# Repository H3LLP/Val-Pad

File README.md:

# Val Pad

A custom half-ish keyboard for gaming

I wanted to make something fun and that I could actually use daily, so I made this. I needed the desk space as well since my mouse didn't have much room to move around, so this is my solution.
  - Magnetically closing case
  - 19 switches
  - knob
  - gasket-mounted
  - https://www.printables.com/model/1851866-val-pad
  - Uses QMK Firmware(partly made with AI)

# Electric Bits

PCB Schematics

# BOM
|Designator                                                                               |Footprint                                                           |Quantity|Value                                             |Price |
|-----------------------------------------------------------------------------------------|--------------------------------------------------------------------|--------|--------------------------------------------------|------|
|D1, D10, D11, D12, D13, D14, D15, D16, D17, D18, D19, D2, D20, D3, D4, D5, D6, D7, D8, D9|D_DO-35_SOD27_P7.62mm_Horizontal                                    |20      |1N4148 (THT) Diode                                |$5    |
|S1, S10, S11, S12, S13, S14, S15, S16, S17, S18, S19, S2, S3, S4, S5, S6, S7, S8, S9     |MX_PCB_1.00u                                                        |19      |MX Switches                                       |$20   |
|SW1                                                                                      |RotaryEncoder_Alps_EC11E-Switch_Vertical_H20mm_CircularMountingHoles|1       |EC11 Rotary Encoder                               |$5    |
|U1                                                                                       |SOIC-28W_7.5x17.9mm_P1.27mm                                         |1       |MCP23017 Surface Mounted                          |$2    |
|U2                                                                                       |Seeed_XIAO_RP2040                                                   |1       |Seeed Xiao RP2040                                 |$7    |
|R1, R2                                                                                   |0603                                                                |2       |4.7 kΩ 0603 package 1/10 W surface-mount resistors|$3    |
|~                                                                                        |~                                                                   |1       |PCB                                               |$5    |
|~                                                                                        |~                                                                   |4       |4mm*2mm Circular Neodymium Magnets                |$10   |
|~                                                                                        |~                                                                   |4       |4mm*30mm Keyboard Gasket Strips                   |$7    |
|~                                                                                        |~                                                                   |4       |3D Printed Parts                                  |$10   |
|~                                                                                        |~                                                                   |4       |Macbook Pro Rubber Feet                           |$5    |
|~                                                                                        |~                                                                   |1       |Set of 2U PCB Mounted MX Stabilizers              |$10   |
|~                                                                                        |~                                                                   |15      |1U Keycaps                                        |varies|
|~                                                                                        |~                                                                   |1       |1.25U Keycaps                                     |varies|
|~                                                                                        |~                                                                   |2       |1.5U Keycaps                                      |varies|
|~                                                                                        |~                                                                   |1       |2U Keycap                                         |varies|
|~                                                                                        |~                                                                   |~       |~                                                 |Total $ 110-120|

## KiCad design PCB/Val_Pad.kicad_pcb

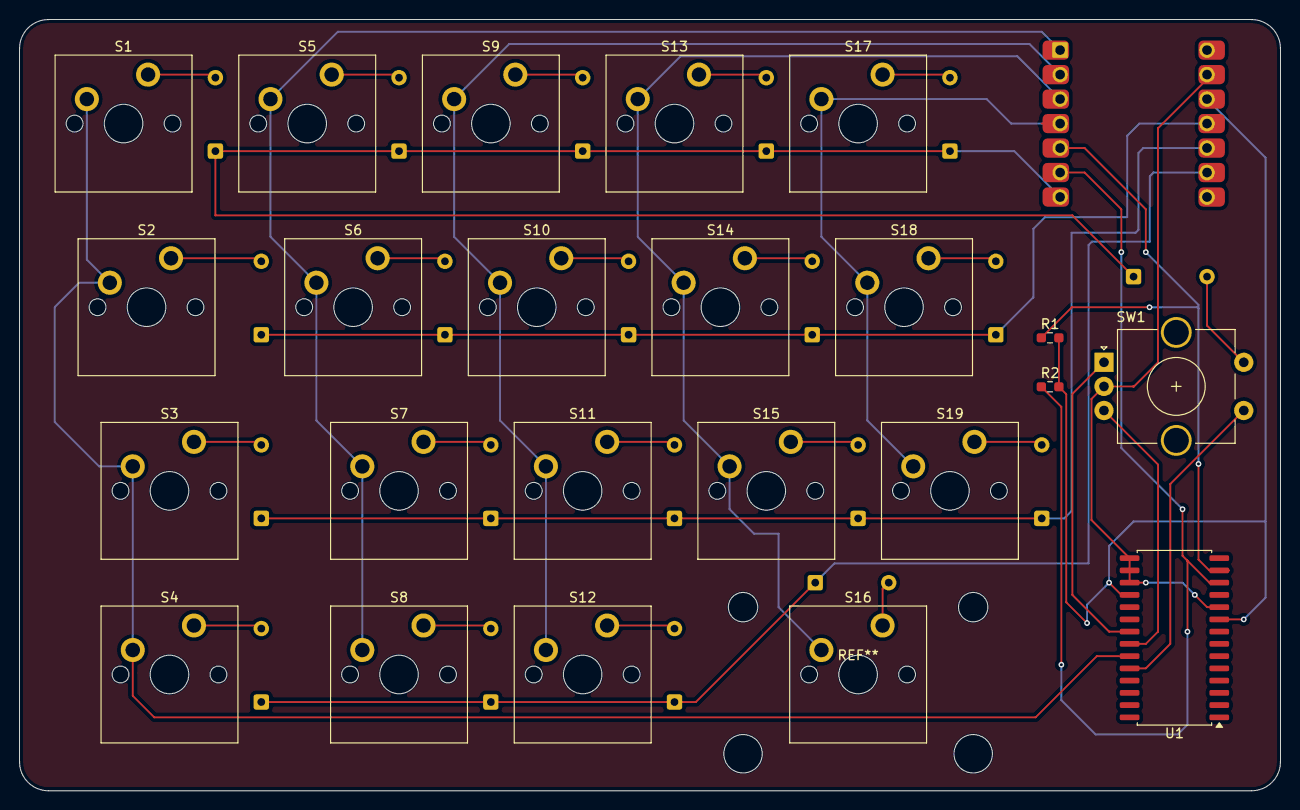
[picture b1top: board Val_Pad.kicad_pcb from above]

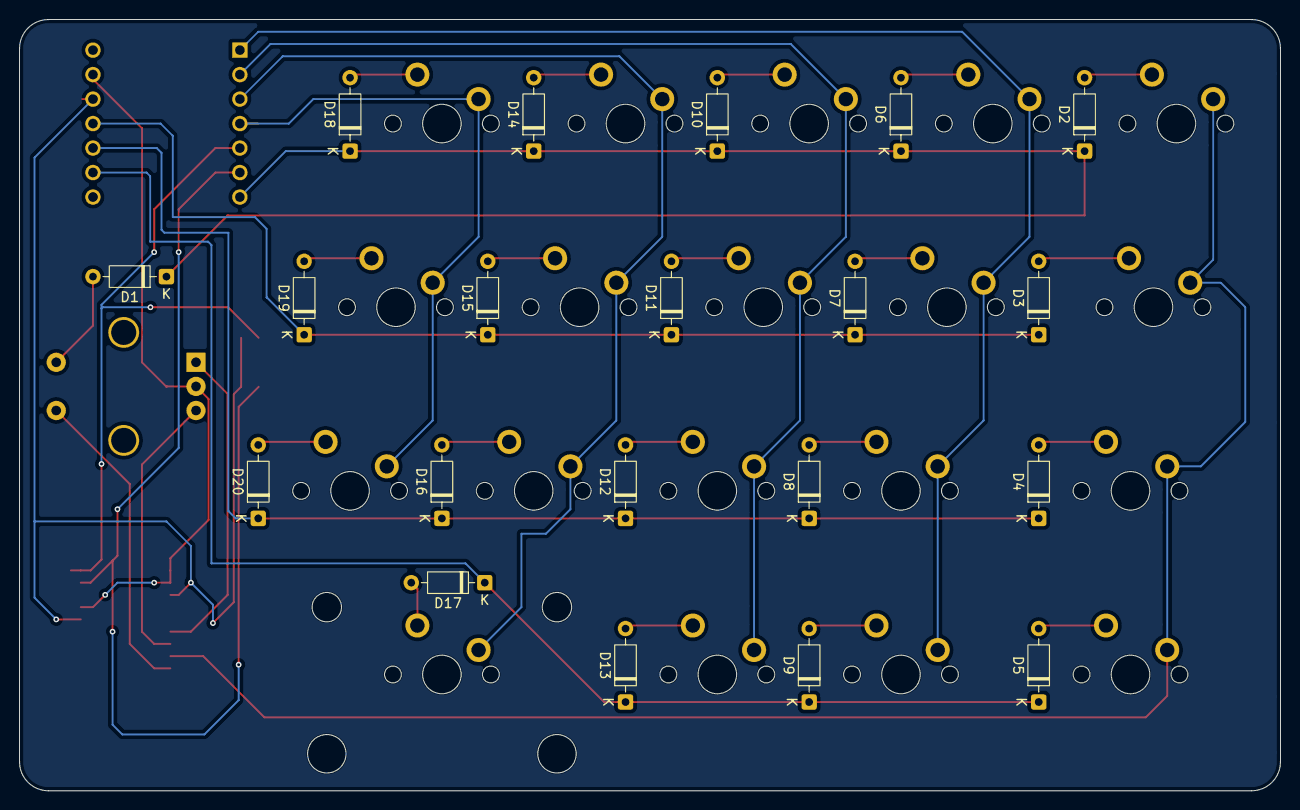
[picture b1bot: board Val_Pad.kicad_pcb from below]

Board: 2 copper layers, 130.8 x 80.0 mm, 44 parts (20 on the bottom side), 36 nets.

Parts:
D1, D2, D3, D4, D5, D6, D7, D8, D9, D10, D11, D12, D13, D14, D15, D16, D17, D18, D19, D20: D_DO-35_SOD27_P7.62mm_Horizontal
R1, R2: R; R_0603_1608Metric_Pad0.98x0.95mm_HandSolder
S1, S2, S3, S4, S5, S6, S7, S8, S9, S10, S11, S12, S13, S14, S15, S16, S17, S18, S19: MX_PCB_1.00u
SW1: RotaryEncoder_Switch; RotaryEncoder_Alps_EC11E-Switch_Vertical_H20mm_CircularMoun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
U1: MCP23017x-x-SO; SOIC-28W_7.5x17.9mm_P1.27mm
U2: MCU_Seeed_XIAO_RP2040; Seeed_XIAO_RP2040

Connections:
/A: SW1.A, U1.21 (GPA0)
/B: SW1.B, U1.22 (GPA1)
/C: SW1.C, U1.10 (V_{SS}), U1.15 (A0), U1.16 (A1), U1.17 (A2), U2.13 (GND)
/Column 0: S1.1, S2.1, S3.1, S4.1, U1.23 (GPA2)
/Column 1: S5.1, S6.1, S7.1, S8.1, U2.1 (PA02_A0_D0)
/Column 2: S9.1, S10.1, S11.1, S12.1, U2.2 (PA4_A1_D1)
/Column 3: S13.1, S14.1, S15.1, S16.1, U2.3 (PA10_A2_D2)
/Column 4: S17.1, S18.1, S19.1, U2.4 (PA11_A3_D3)
/Column -1: SW1.S1, U1.24 (GPA3)
/Row 0: D1.1 (K), D2.1 (K), D6.1 (K), D10.1 (K), D14.1 (K), D18.1 (K), U2.7 (PB08_A6_D6_TX)
/Row 1: D3.1 (K), D7.1 (K), D11.1 (K), D15.1 (K), D19.1 (K), U2.11 (PA6_A10_D10_MOSI)
/Row 2: D4.1 (K), D8.1 (K), D12.1 (K), D16.1 (K), D20.1 (K), U2.10 (PA5_A9_D9_MISO)
/Row 3: D5.1 (K), D9.1 (K), D13.1 (K), D17.1 (K), U2.9 (PA7_A8_D8_SCK)
unnamed: D1.2 (A), SW1.S2
unnamed: D2.2 (A), S1.2
unnamed: D3.2 (A), S2.2
unnamed: D4.2 (A), S3.2
unnamed: D5.2 (A), S4.2
unnamed: D6.2 (A), S5.2
unnamed: D7.2 (A), S6.2
unnamed: D8.2 (A), S7.2
unnamed: D9.2 (A), S8.2
unnamed: D10.2 (A), S9.2
unnamed: D11.2 (A), S10.2
unnamed: D12.2 (A), S11.2
unnamed: D13.2 (A), S12.2
unnamed: D14.2 (A), S13.2
unnamed: D15.2 (A), S14.2
unnamed: D16.2 (A), S15.2
unnamed: D17.2 (A), S16.2
unnamed: D18.2 (A), S17.2
unnamed: D19.2 (A), S18.2
unnamed: D20.2 (A), S19.2
unnamed: R2.1, U1.12 (SCK), U2.6 (PA9_A5_D5_SCL)
unnamed: R1.1, U1.13 (SDA), U2.5 (PA8_A4_D4_SDA)
unnamed: R1.2, R2.2, U1.9 (V_{DD}), U1.18 (~RESET), U2.12 (3V3)
